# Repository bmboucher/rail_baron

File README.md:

# pyrailbaron

An electronic implementation of the classic board game **Rail Baron**,
spanning a Python game engine, a touchscreen GUI, a CAD-derived map
pipeline, and custom hardware (Teensy firmware + PCB) for a physical
board with LED indicators.

## Components

| Path        | What it is                                                        |
|-------------|-------------------------------------------------------------------|
| `python/`   | The `pyrailbaron` package: game rules, AI, pygame GUI, and CLI.   |
| `python/src/pyrailbaron/game/`  | Core game loop, state model, AI, fees, and per-screen GUI. |
| `python/src/pyrailbaron/map/`   | Map ETL: parses railroad geometry from DXF CAD files, fits/simplifies paths, and renders SVG maps. |
| `python/src/pyrailbaron/teensy/`| Serial protocol used to drive the physical board's LEDs/displays. |
| `teensy/`   | PlatformIO firmware (C++) for the Teensy microcontroller, incl. a TM1637 7-segment driver. |
| `pcb/`      | EAGLE schematic/board files ("tophat") for the custom control PCB. |
| `data/`     | Map data: city labels, region borders, payoff & roll tables, DXF sources, generated `map.json`. |

## Quick start (software game)

```bash
cd python
python -m venv .venv
source .venv/bin/activate      # .\.venv\Scripts\Activate.ps1 on Windows
pip install -e .
railbaron                       # console entry point (pyrailbaron.game.main)
```

Requires Python 3.x with `pygame >= 2.0`. Other dependencies
(`ezdxf`, `svgwrite`, `numpy`, `sklearn`, `dataclasses-json`) are in
`python/requirements.txt` and are used mainly by the map ETL scripts.

## Map pipeline

The board map is built from DXF CAD exports in `data/dxf/`. Scripts in
`python/scripts/` (e.g. `scrape_dxf.py`, `simplify_rr_paths.py`) extract
and simplify each railroad's geometry; the `pyrailbaron.map` package fits
coordinates, draws state/region borders, and emits SVG + `map.json`.

## Hardware

The physical board uses a Teensy microcontroller (firmware in `teensy/`,
built with PlatformIO) on a custom PCB (`pcb/tophat.*`, EAGLE format).
The Python game talks to the board over a simple serial protocol defined
in `pyrailbaron/teensy/serial.py` (active-player LED, region/destination
highlights, bank/ownership displays).

## License

GPL — see [LICENSE](LICENSE).

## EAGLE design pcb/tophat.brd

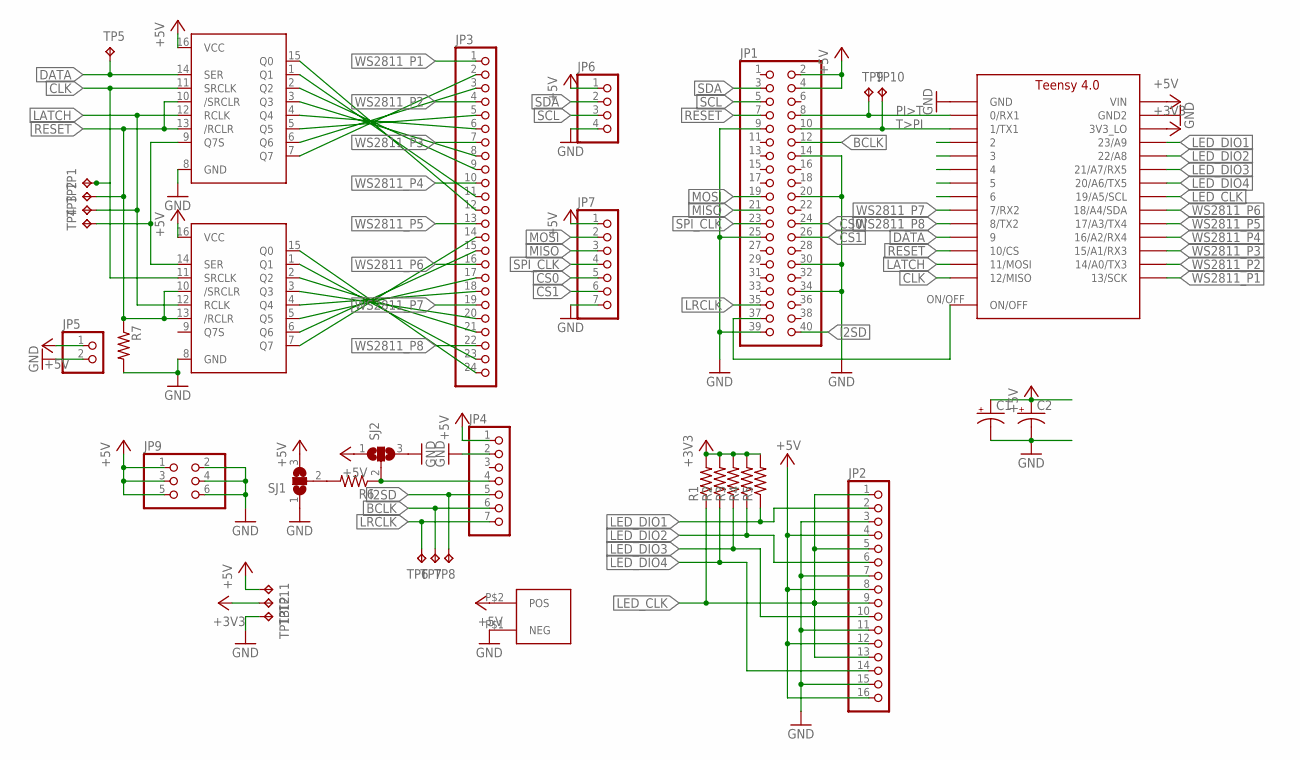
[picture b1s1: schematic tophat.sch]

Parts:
C1, C2: CPOL-USE5-10.5; E5-10,5
JP1: PINHD-2X20; 2X20
JP2: PINHD-1X16/90; 1X16/90
JP3: PINHD-1X24/90; 1X24/90
JP4, JP7: PINHD-1X7; 1X07
JP5: PINHD-1X2; 1X02
JP6: PINHD-1X4; 1X04
JP8: PWR_CONN
JP9: PINHD-2X3; 2X03
R1, R2, R3, R4, R5, R6, R7: R-US_0207/10; 0207/10
SJ1, SJ2: SJ2W; SJ_2
TP1, TP2, TP3, TP4, TP5, TP6, TP7, TP8, TP9, TP10, TP11, TP12, TP13: TPB2,54; B2,54
U$1: TEENSY_4.0
U$2, U$3: 74AHCT95; SOIC127P600X175-16N

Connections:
+3V3: R1.2, R2.2, R3.2, R4.2, R5.2, TP12.TP, U$1.3V3_LO
+5V: C1.+, C2.+, JP1.2, JP1.4, JP2.4, JP2.8, JP2.12, JP2.16, JP4.1, JP5.1, JP6.1, JP7.1, JP8.P$2 (POS), JP9.1, JP9.3, JP9.5, SJ1.3, SJ2.1, TP11.TP, U$1.VIN, U$2.16 (VCC), U$3.16 (VCC)
BCLK: JP1.12, JP4.6, TP7.TP
CLK: TP1.TP, U$1.12/MISO, U$2.11 (SRCLK), U$3.11 (SRCLK)
CS0: JP1.24, JP7.5
CS1: JP1.26, JP7.6
DATA: TP5.TP, U$1.9/CS (9), U$2.14 (SER)
GND: C1.-, C2.-, JP1.9, JP1.14, JP1.20, JP1.25, JP1.30, JP1.34, JP1.39, JP2.3, JP2.7, JP2.11, JP2.15, JP4.2, JP5.2, JP6.4, JP7.7, JP8.P$1 (NEG), JP9.2, JP9.4, JP9.6, R7.2, SJ1.1, SJ2.3, TP13.TP, U$1.GND, U$1.GND2, U$2.8 (GND), U$3.8 (GND)
I2SD: JP1.40, JP4.5, TP8.TP
LATCH: TP3.TP, U$1.11/MOSI, U$2.12 (RCLK), U$3.12 (RCLK)
LED_CLK: JP2.1, JP2.5, JP2.9, JP2.13, R1.1, U$1.19/A5/SCL
LED_DIO1: JP2.2, R5.1, U$1.23/A9
LED_DIO2: JP2.6, R4.1, U$1.22/A8
LED_DIO3: JP2.10, R3.1, U$1.21/A7 (21/A7/RX5)
LED_DIO4: JP2.14, R2.1, U$1.20/A6 (20/A6/TX5)
LRCLK: JP1.35, JP4.7, TP6.TP
MISO: JP1.21, JP7.3
MOSI: JP1.19, JP7.2
unnamed: TP4.TP, U$2.9 (Q7S), U$3.14 (SER)
unnamed: JP1.37, U$1.ON/OFF
unnamed: JP3.2, U$2.7 (Q7)
unnamed: JP3.3, U$2.6 (Q6)
unnamed: JP3.5, U$2.5 (Q5)
unnamed: JP3.6, U$2.4 (Q4)
unnamed: JP3.8, U$2.3 (Q3)
unnamed: JP3.9, U$2.2 (Q2)
unnamed: JP3.11, U$2.1 (Q1)
unnamed: JP3.12, U$2.15 (Q0)
unnamed: JP3.14, U$3.7 (Q7)
unnamed: JP3.15, U$3.6 (Q6)
unnamed: JP3.17, U$3.5 (Q5)
unnamed: JP3.18, U$3.4 (Q4)
unnamed: JP3.20, U$3.3 (Q3)
unnamed: JP3.21, U$3.2 (Q2)
unnamed: JP3.23, U$3.1 (Q1)
unnamed: JP3.24, U$3.15 (Q0)
unnamed: JP4.4, R6.1, SJ2.2
unnamed: R6.2, SJ1.2
PI>T: JP1.8, TP9.TP, U$1.0/RX (0/RX1)
RESET: JP1.7, R7.1, TP2.TP, U$1.10/CS, U$2.10 (/SRCLR), U$2.13 (/RCLR), U$3.10 (/SRCLR), U$3.13 (/RCLR)
SCL: JP1.5, JP6.3
SDA: JP1.3, JP6.2
SPI_CLK: JP1.23, JP7.4
T>PI: JP1.10, TP10.TP, U$1.1/TX (1/TX1)
WS2811_P1: JP3.1, U$1.13/SCK
WS2811_P2: JP3.4, U$1.14/A0 (14/A0/TX3)
WS2811_P3: JP3.7, U$1.15/A1 (15/A1/RX3)
WS2811_P4: JP3.10, U$1.16/A2 (16/A2/RX4)
WS2811_P5: JP3.13, U$1.17/A3 (17/A3/TX4)
WS2811_P6: JP3.16, U$1.18/A4/SDA
WS2811_P7: JP3.19, U$1.7 (7/RX2)
WS2811_P8: JP3.22, U$1.8 (8/TX2)

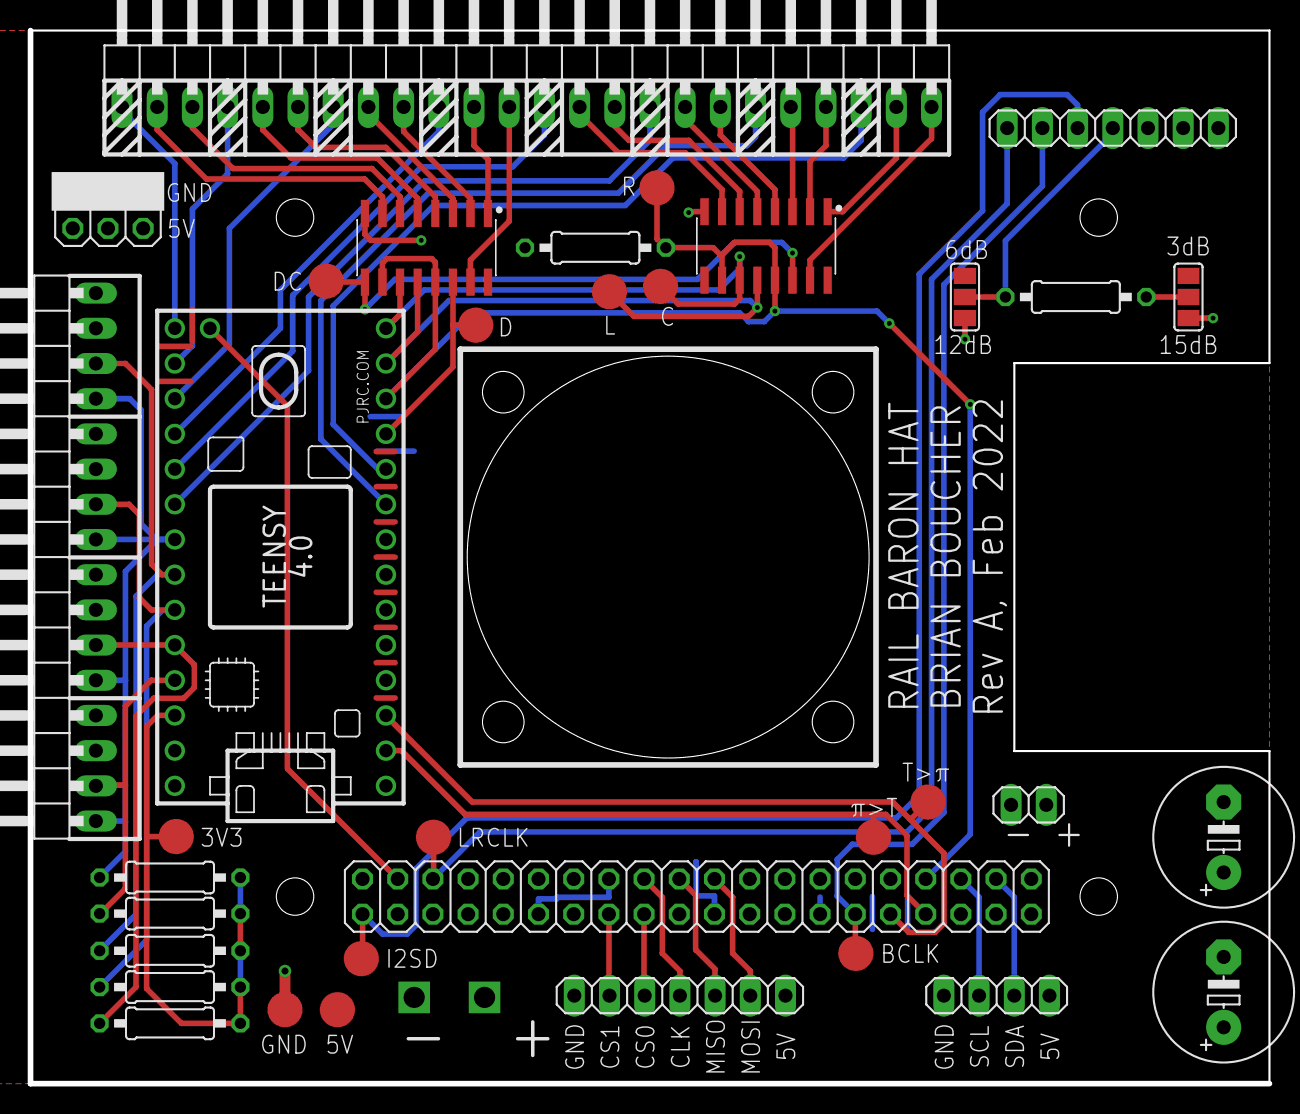
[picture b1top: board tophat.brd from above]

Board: 2 copper layers, 89.4 x 76.0 mm, 36 parts (0 on the bottom side), 52 nets.

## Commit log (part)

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2021-12-05 Initial DXFs taken from scanned map
2021-12-06 Adding scrape_dxf script to parse captured data from Fusion
2021-12-07 Initial SVG generation and lookup of city coordinates
2021-12-07 Reorganizing search_coord
2021-12-09 Starting on pyrailbaron.map module
2021-12-14 Initial population of states and regions (NORTHEAST and SOUTHEAST)
2021-12-14 Adding SVG region colors
2021-12-15 Finished all regions and added cities
2021-12-15 Adding city labels
2021-12-16 Cleaning up draw.py
2021-12-16 Adding multiple rails to draw.py
2021-12-17 Completed patterns for all railroads
2021-12-17 Adding triangles
2021-12-17 Tweaking label locations
2021-12-20 Checking in map.json
2021-12-22 Updating map drawing
2021-12-22 Adding canada (needs more work)
2021-12-22 Adding some RR labels
2021-12-22 Adding canada
2021-12-23 Adding mexico
2021-12-23 Adding aluminum and acrylic layers
2021-12-28 Adding test piece
2021-12-28 Starting pygame component
2021-12-28 Starting initial game logic
2021-12-29 Finished outline of game logic
2021-12-30 Adding payoffs
2021-12-30 Completing game logic
2021-12-30 Adding roll tables
2021-12-30 Updates after strict type checking, and implementing CLI interface
2021-12-31 Working test of CLI
2021-12-31 Minor tweaks, starting on AI
2021-12-31 Adding AI to the move logic
2022-01-01 Updating game logic/AI
2022-01-01 Updating logic to pass user fees to purchase interface
2022-01-02 Working AI (except for declaring and auctions)
2022-01-02 More tweaks to AI
2022-01-03 Fully working AI and game logic, plays itself forever
2022-01-04 Adding simplified paths
2022-01-04 Starting GUI
2022-01-04 Initial main menu
2022-01-05 Adding die roll and keyboard screens
2022-01-05 Fixing rover re-planning logic
2022-01-05 Finalizing player name keyboard
2022-01-05 Integrating player name keyboard into game logic w/randomized order
2022-01-05 Adding stub methods to make PyGameInterface a valid instance of Interface
2022-01-05 Updates to roll screen
2022-01-05 Starting stub of serial to teensy
2022-01-05 Starting move screen
2022-01-06 Updates with working move screen
2022-01-06 Fixing draw
2022-01-07 Move screen with real map
2022-01-09 Working move and purchase select screens
2022-01-12 Working GUI up to choose sell/auction
2022-01-12 Adding auction screen
2022-01-13 Adding declare screen
2022-01-13 Adding player order screen
2022-01-13 Add shortfall screen
2022-01-13 Finish last screens
2022-01-13 Updating logic so undeclared/rover play notices don't dupe
2022-01-14 Adding calculation of expected region payoffs
2022-02-04 Adding initial PlatformIO project for Teensy firmware
2022-02-04 Updating .gitignores
2022-02-04 Adding tophat pcb
2022-03-04 3-3-22 Updates
